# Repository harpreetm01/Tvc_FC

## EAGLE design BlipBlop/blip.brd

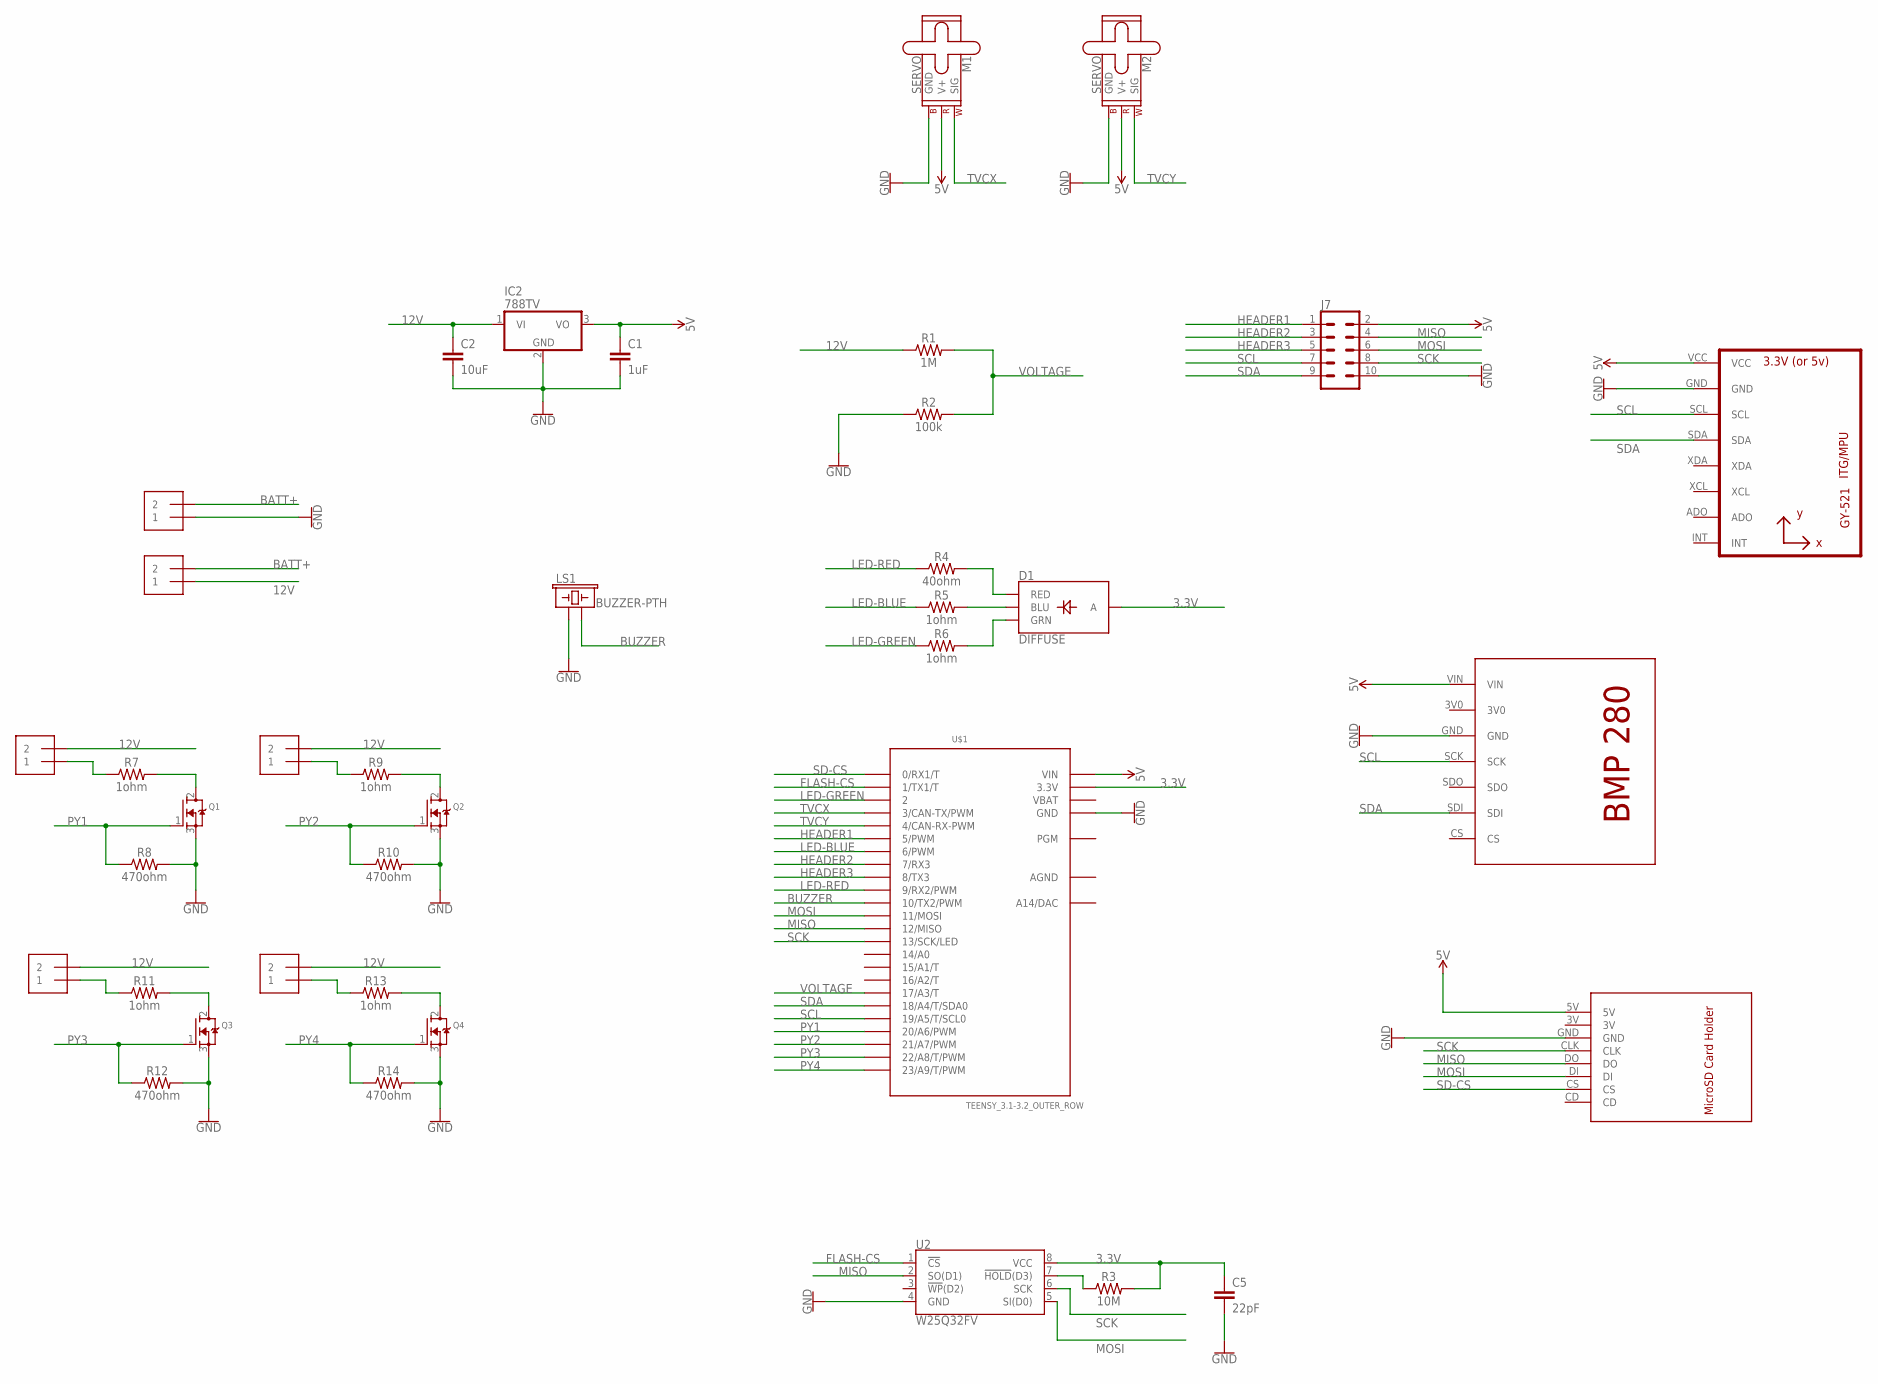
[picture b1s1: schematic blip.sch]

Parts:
C1: 1uF; CAP-PTH-2.54
C2: 10uF; CAP-PTH-2.54
C5: 22pF; CAP-PTH-2.54
D1: DIFFUSE; LED-RGB-THRU
IC2: 788TV; TO220V
J1, J2, J3, J4, J5, J6: 1X2-3.5MM
J7: CONN_05X2NO_SILK; 2X5_NOSILK
LS1: BUZZER-PTH; BUZZER-12MM
M1, M2: SERVO; 1X03
Q1, Q2, Q3, Q4: MOSFET-NGDS_TO220V; TO220V
R1: 1M; AXIAL-0.3
R2: 100k; AXIAL-0.3
R3: 10M; AXIAL-0.3
R4: 40ohm; AXIAL-0.3
R5, R6, R7, R9, R11, R13: 1ohm; AXIAL-0.3
R8, R10, R12, R14: 470ohm; AXIAL-0.3
U1: GY-521MPU6050; GY-521
U2: W25Q32FV; SOIC-8
U$1: TEENSY_3.1-3.2_OUTER_ROW; TEENSY_3.0-3.2&LC_OUTER_ROW
U$2: BMP280
U$3: SDCARD

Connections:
3.3V: C5.1, D1.2 (A), R3.P$2 (2), U2.8 (VCC), U$1.3.3V, U$1.3.3V1 (3.3V)
5V: C1.1, IC2.3 (VO), J7.2, M1.2 (V+), M2.2 (V+), U1.VCC, U$1.VIN, U$2.VIN, U$3.5V
12V: C2.1, IC2.1 (VI), J2.1, J3.2, J4.2, J5.2, J6.2, R1.P$1 (1)
AGND: U$1.AGND
BATT+: J1.2, J2.2
BUZZER: LS1.- (2), U$1.10 (10/TX2/PWM)
FLASH-CS: U2.1 (!CS!), U$1.1 (1/TX1/T)
GND: C1.2, C2.2, C5.2, IC2.2 (GND), J1.1, J7.10, LS1.+ (1), M1.3 (GND), M2.3 (GND), Q1.3 (S), Q2.3 (S), Q3.3 (S), Q4.3 (S), R2.P$1 (1), R8.P$2 (2), R10.P$2 (2), R12.P$2 (2), R14.P$2 (2), U1.GND, U2.4 (GND), U$1.GND, U$1.GND1 (GND), U$2.GND, U$3.GND
HEADER1: J7.1, U$1.5 (5/PWM)
HEADER2: J7.3, U$1.7 (7/RX3)
HEADER3: J7.5, U$1.8 (8/TX3)
LED-BLUE: R5.P$1 (1), U$1.6 (6/PWM)
LED-GREEN: R6.P$1 (1), U$1.2
LED-RED: R4.P$1 (1), U$1.9 (9/RX2/PWM)
MISO: J7.4, U2.2 (SO(D1)), U$1.12 (12/MISO), U$3.DO
MOSI: J7.6, U2.5 (SI(D0)), U$1.11 (11/MOSI), U$3.DI
unnamed: R3.P$1 (1), U2.7 (!HOLD!(D3))
unnamed: D1.4 (BLU), R5.P$2 (2)
unnamed: D1.3 (GRN), R6.P$2 (2)
unnamed: D1.1 (RED), R4.P$2 (2)
unnamed: J3.1, R7.P$1 (1)
unnamed: Q1.2 (D), R7.P$2 (2)
unnamed: J4.1, R9.P$1 (1)
unnamed: Q2.2 (D), R9.P$2 (2)
unnamed: J5.1, R11.P$1 (1)
unnamed: Q3.2 (D), R11.P$2 (2)
unnamed: J6.1, R13.P$1 (1)
unnamed: Q4.2 (D), R13.P$2 (2)
PY1: Q1.1 (G), R8.P$1 (1), U$1.20/A6 (20/A6/PWM)
PY2: Q2.1 (G), R10.P$1 (1), U$1.21/A7 (21/A7/PWM)
PY3: Q3.1 (G), R12.P$1 (1), U$1.22/A8 (22/A8/T/PWM)
PY4: Q4.1 (G), R14.P$1 (1), U$1.23/A9 (23/A9/T/PWM)
SCK: J7.8, U2.6 (SCK), U$1.13 (13/SCK/LED), U$3.CLK
SCL: J7.7, U1.SCL, U$1.19/A5 (19/A5/T/SCL0), U$2.SCK
SD-CS: U$1.0 (0/RX1/T), U$3.CS
SDA: J7.9, U1.SDA, U$1.18/A4 (18/A4/T/SDA0), U$2.SDI
TVCX: M1.1 (SIG), U$1.3 (3/CAN-TX/PWM)
TVCY: M2.1 (SIG), U$1.4 (4/CAN-RX-PWM)
VBAT: U$1.VBAT
VOLTAGE: R1.P$2 (2), R2.P$2 (2), U$1.17/A3 (17/A3/T)

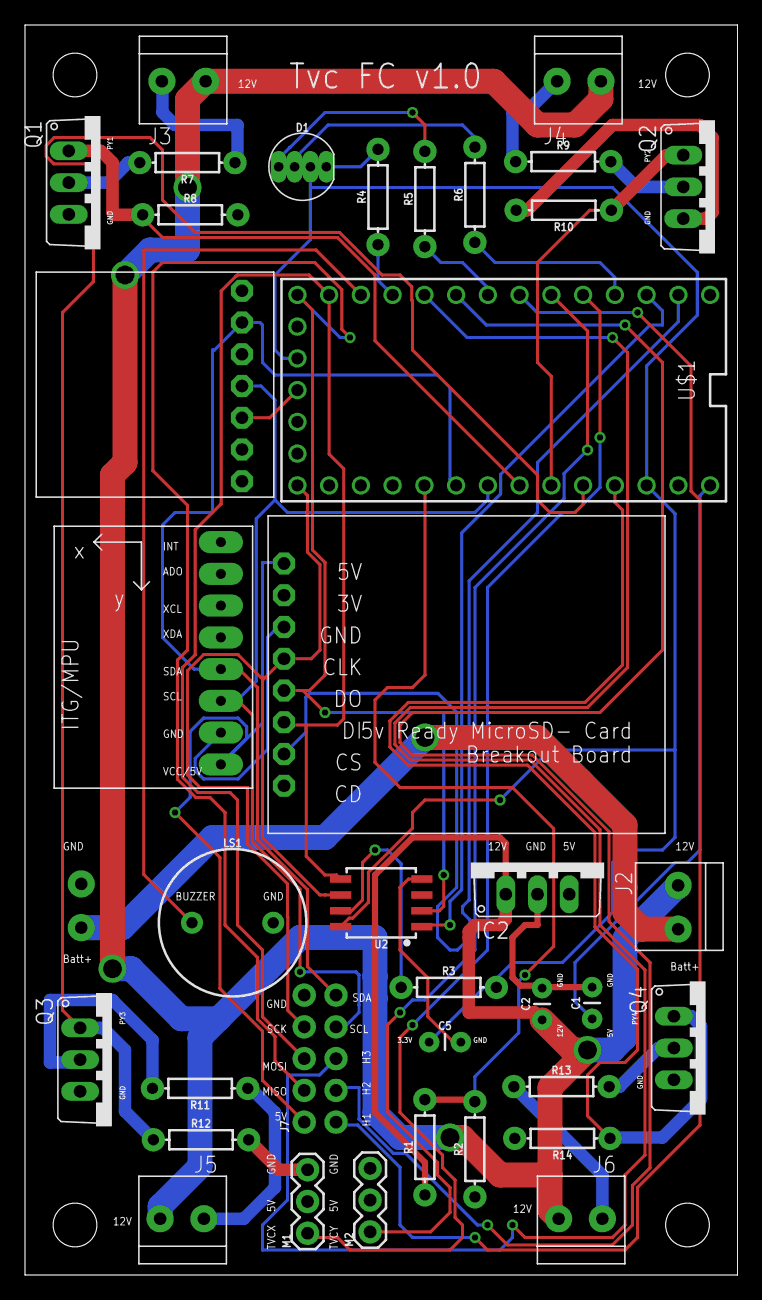
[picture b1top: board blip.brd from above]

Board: 2 copper layers, 57.0 x 100.0 mm, 38 parts (1 on the bottom side), 38 nets.

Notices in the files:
parts and their libraries:
SparkFun-Capacitors: Licensing: Creative Commons ShareAlike 4.0 International - https://creativecommons.org/licenses/by-sa/4.0
